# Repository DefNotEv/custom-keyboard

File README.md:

A description of what your project is
A couple sentences on why you made the project

# piggy keyboard!!!

## description
this is a super basic 60% keyboard with akko steller rose switches. it's completely custom: the pcb, cad, and plate files are all in here. 

## why i made it!
i've been talking about making a keyboard since the pandemic started but i am BROKE (that's a fancy way of saying i'm lazy) so when i found out i can do it all FOR FREE??? HELLO???? YES PLEASE??? 

## but uh...
bro initially i wanted to make this a tkl but tell me why kicad keybaord schematics are so difficult and for what??? like an rp2040 is NOT that complicated why am i struggling to trace capacitors. anyway. had to dumb it down. i hope i can make another tkl later. somebody please teach me how to proprely make pcbs.

## stfu ev show me the pictures
i gotchu

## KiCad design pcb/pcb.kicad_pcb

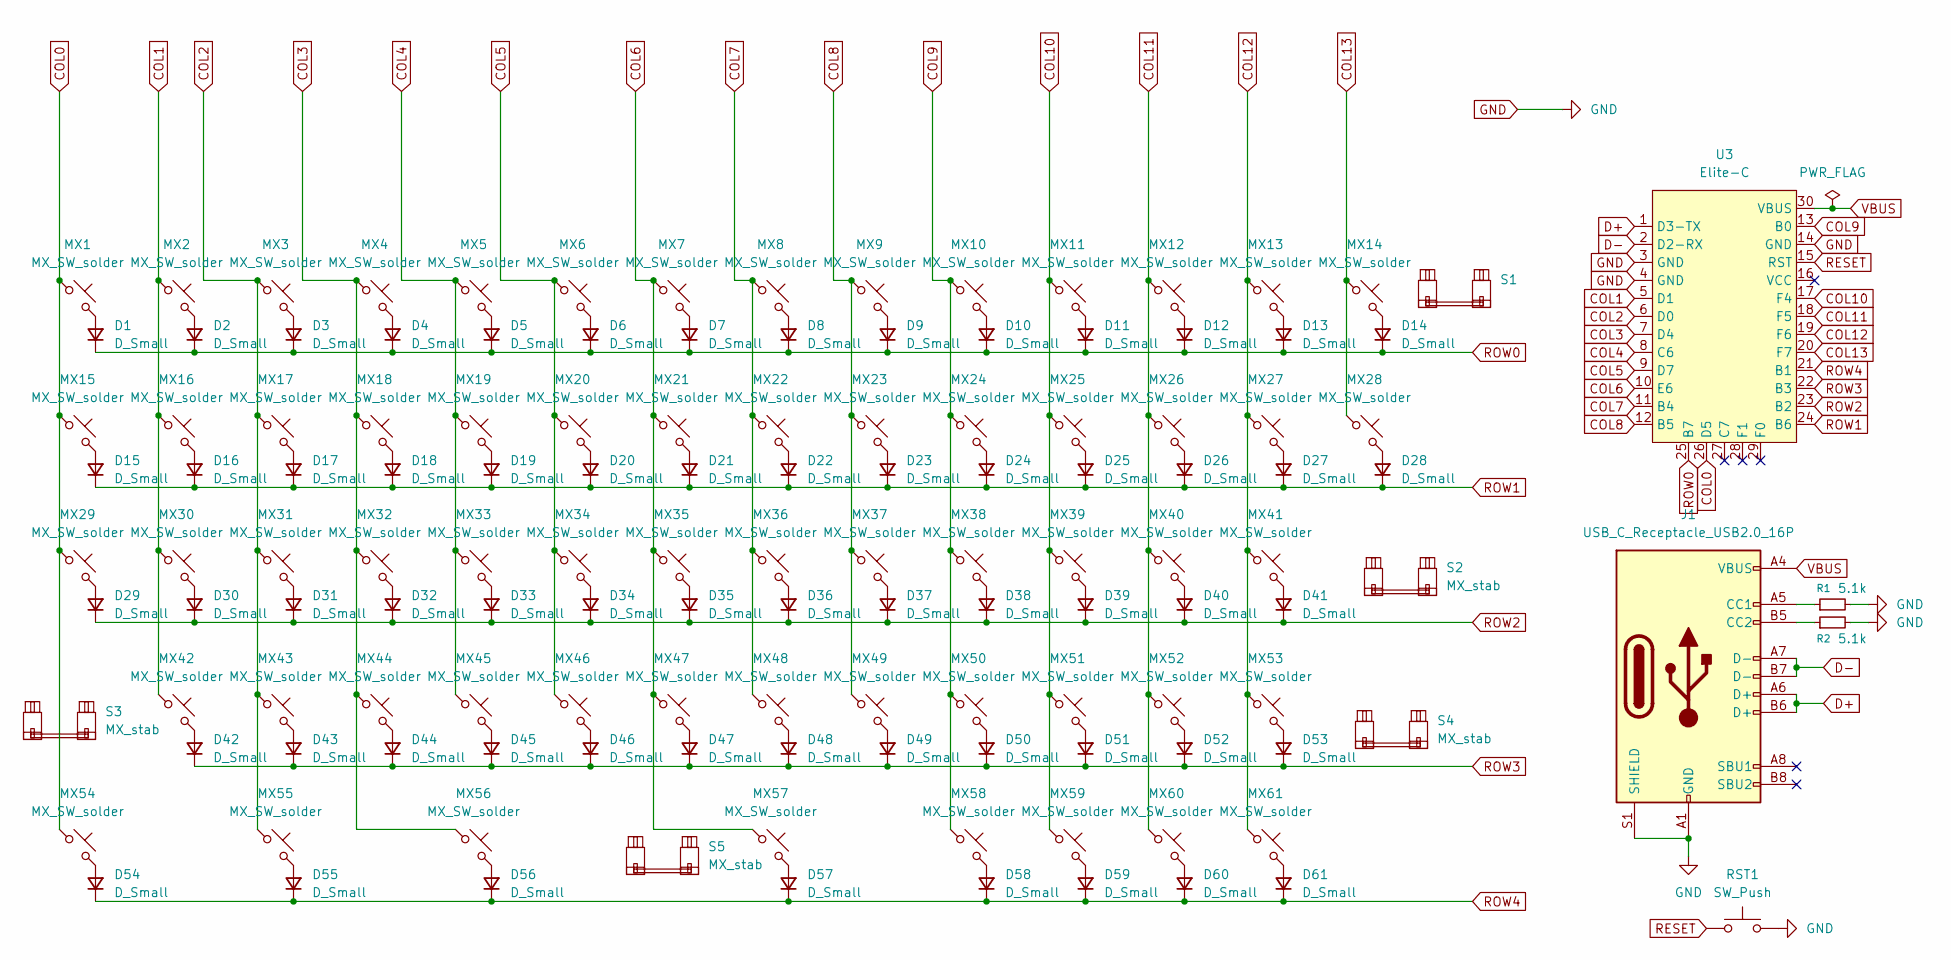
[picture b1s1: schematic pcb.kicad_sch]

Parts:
D1, D2, D3, D4, D5, D6, D7, D8, D9, D10, D11, D12, D13, D14, D15, D16, D17, D18, D19, D20, D21, D22, D23, D24, D25, D26, D27, D28, D29, D30, D31, D32, D33, D34, D35, D36, D37, D38, D39, D40, D41, D42, D43, D44, D45, D46, D47, D48, D49, D50, D51, D52, D53, D54, D55, D56, D57, D58, D59, D60, D61: D_Small; D_SOD-123
J1: USB_C_Receptacle_USB2.0_16P; USB_C_Receptacle_HRO_TYPE-C-31-M-12
MX1, MX2, MX3, MX4, MX5, MX6, MX7, MX8, MX9, MX10, MX11, MX12, MX13, MX14, MX16, MX17, MX18, MX19, MX20, MX21, MX22, MX23, MX24, MX25, MX26, MX27, MX30, MX31, MX32, MX33, MX34, MX35, MX36, MX37, MX38, MX39, MX40, MX41, MX42, MX43, MX44, MX45, MX46, MX47, MX48, MX49, MX50, MX51, MX52, MX53, MX57: MX_SW_solder; SW_MX_1u
MX15, MX28: MX_SW_solder; SW_MX_1.5u
MX29: MX_SW_solder; SW_MX_1.75u
MX54, MX55, MX56, MX58, MX59, MX60, MX61: MX_SW_solder; SW_MX_1.25u
R1, R2: 5.1k; R_0402_1005Metric
RST1: SW_Push; SW_SPST_TL3305B
S1, S2, S3, S4: MX_stab; STAB_MX_P_2u
S5: MX_stab; STAB_MX_P_6.25u
U3: Elite-C; Elite-C_ACH

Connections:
COL0: MX1.1, MX15.1, MX29.1, MX54.1, U3.26 (D5)
COL1: MX2.1, MX16.1, MX30.1, MX42.1, U3.5 (D1)
COL2: MX3.1, MX17.1, MX31.1, MX43.1, MX55.1, U3.6 (D0)
COL3: MX4.1, MX18.1, MX32.1, MX44.1, MX56.1, U3.7 (D4)
COL4: MX5.1, MX19.1, MX33.1, MX45.1, U3.8 (C6)
COL5: MX6.1, MX20.1, MX34.1, MX46.1, U3.9 (D7)
COL6: MX7.1, MX21.1, MX35.1, MX47.1, MX57.1, U3.10 (E6)
COL7: MX8.1, MX22.1, MX36.1, MX48.1, U3.11 (B4)
COL8: MX9.1, MX23.1, MX37.1, MX49.1, U3.12 (B5)
COL9: MX10.1, MX24.1, MX38.1, MX50.1, MX58.1, U3.13 (B0)
COL10: MX11.1, MX25.1, MX39.1, MX51.1, MX59.1, U3.17 (F4)
COL11: MX12.1, MX26.1, MX40.1, MX52.1, MX60.1, U3.18 (F5)
COL12: MX13.1, MX27.1, MX41.1, MX53.1, MX61.1, U3.19 (F6)
COL13: MX14.1, MX28.1, U3.20 (F7)
D+: J1.A6 (D+), J1.B6 (D+), U3.1 (D3-TX)
D-: J1.A7 (D-), J1.B7 (D-), U3.2 (D2-RX)
GND: J1.A1 (GND), J1.A12 (GND), J1.B1 (GND), J1.B12 (GND), J1.S1 (SHIELD), R1.2, R2.2, RST1.2, U3.3 (GND), U3.4 (GND), U3.14 (GND)
unnamed: D1.2 (A), MX1.2
unnamed: D2.2 (A), MX2.2
unnamed: D3.2 (A), MX3.2
unnamed: D4.2 (A), MX4.2
unnamed: D5.2 (A), MX5.2
unnamed: D6.2 (A), MX6.2
unnamed: D7.2 (A), MX7.2
unnamed: D8.2 (A), MX8.2
unnamed: D9.2 (A), MX9.2
unnamed: D10.2 (A), MX10.2
unnamed: D11.2 (A), MX11.2
unnamed: D12.2 (A), MX12.2
unnamed: D13.2 (A), MX13.2
unnamed: D14.2 (A), MX14.2
unnamed: D15.2 (A), MX15.2
unnamed: D16.2 (A), MX16.2
unnamed: D17.2 (A), MX17.2
unnamed: D18.2 (A), MX18.2
unnamed: D19.2 (A), MX19.2
unnamed: D20.2 (A), MX20.2
unnamed: D21.2 (A), MX21.2
unnamed: D22.2 (A), MX22.2
unnamed: D23.2 (A), MX23.2
unnamed: D24.2 (A), MX24.2
unnamed: D25.2 (A), MX25.2
unnamed: D26.2 (A), MX26.2
unnamed: D27.2 (A), MX27.2
unnamed: D28.2 (A), MX28.2
unnamed: D29.2 (A), MX29.2
unnamed: D30.2 (A), MX30.2
unnamed: D31.2 (A), MX31.2
unnamed: D32.2 (A), MX32.2
unnamed: D33.2 (A), MX33.2
unnamed: D34.2 (A), MX34.2
unnamed: D35.2 (A), MX35.2
unnamed: D36.2 (A), MX36.2
unnamed: D37.2 (A), MX37.2
unnamed: D38.2 (A), MX38.2
unnamed: D39.2 (A), MX39.2
unnamed: D40.2 (A), MX40.2
unnamed: D41.2 (A), MX41.2
unnamed: D42.2 (A), MX42.2
unnamed: D43.2 (A), MX43.2
unnamed: D44.2 (A), MX44.2
unnamed: D45.2 (A), MX45.2
unnamed: D46.2 (A), MX46.2
unnamed: D47.2 (A), MX47.2
unnamed: D48.2 (A), MX48.2
unnamed: D49.2 (A), MX49.2
unnamed: D50.2 (A), MX50.2
unnamed: D51.2 (A), MX51.2
unnamed: D52.2 (A), MX52.2
unnamed: D53.2 (A), MX53.2
unnamed: D54.2 (A), MX54.2
unnamed: D55.2 (A), MX55.2
unnamed: D56.2 (A), MX56.2
unnamed: D57.2 (A), MX57.2
unnamed: D58.2 (A), MX58.2
unnamed: D59.2 (A), MX59.2
unnamed: D60.2 (A), MX60.2
unnamed: D61.2 (A), MX61.2
unnamed: J1.A5 (CC1), R1.1
unnamed: J1.B5 (CC2), R2.1
RESET: RST1.1, U3.15 (RST)
ROW0: D1.1 (K), D2.1 (K), D3.1 (K), D4.1 (K), D5.1 (K), D6.1 (K), D7.1 (K), D8.1 (K), D9.1 (K), D10.1 (K), D11.1 (K), D12.1 (K), D13.1 (K), D14.1 (K), U3.25 (B7)
ROW1: D15.1 (K), D16.1 (K), D17.1 (K), D18.1 (K), D19.1 (K), D20.1 (K), D21.1 (K), D22.1 (K), D23.1 (K), D24.1 (K), D25.1 (K), D26.1 (K), D27.1 (K), D28.1 (K), U3.24 (B6)
ROW2: D29.1 (K), D30.1 (K), D31.1 (K), D32.1 (K), D33.1 (K), D34.1 (K), D35.1 (K), D36.1 (K), D37.1 (K), D38.1 (K), D39.1 (K), D40.1 (K), D41.1 (K), U3.23 (B2)
ROW3: D42.1 (K), D43.1 (K), D44.1 (K), D45.1 (K), D46.1 (K), D47.1 (K), D48.1 (K), D49.1 (K), D50.1 (K), D51.1 (K), D52.1 (K), D53.1 (K), U3.22 (B3)
ROW4: D54.1 (K), D55.1 (K), D56.1 (K), D57.1 (K), D58.1 (K), D59.1 (K), D60.1 (K), D61.1 (K), U3.21 (B1)
VBUS: J1.A4 (VBUS), J1.A9 (VBUS), J1.B4 (VBUS), J1.B9 (VBUS), U3.30 (VBUS)

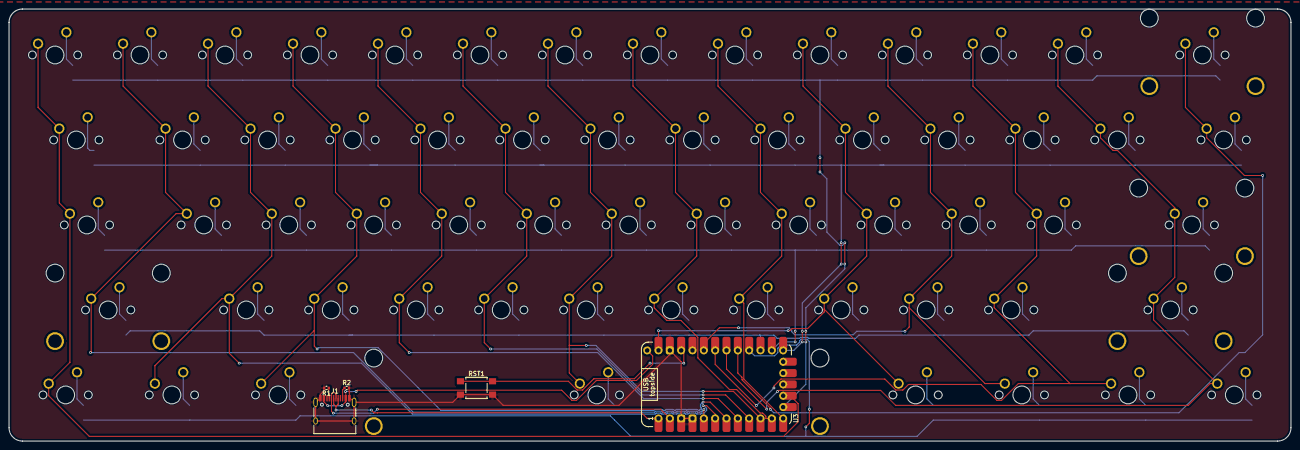
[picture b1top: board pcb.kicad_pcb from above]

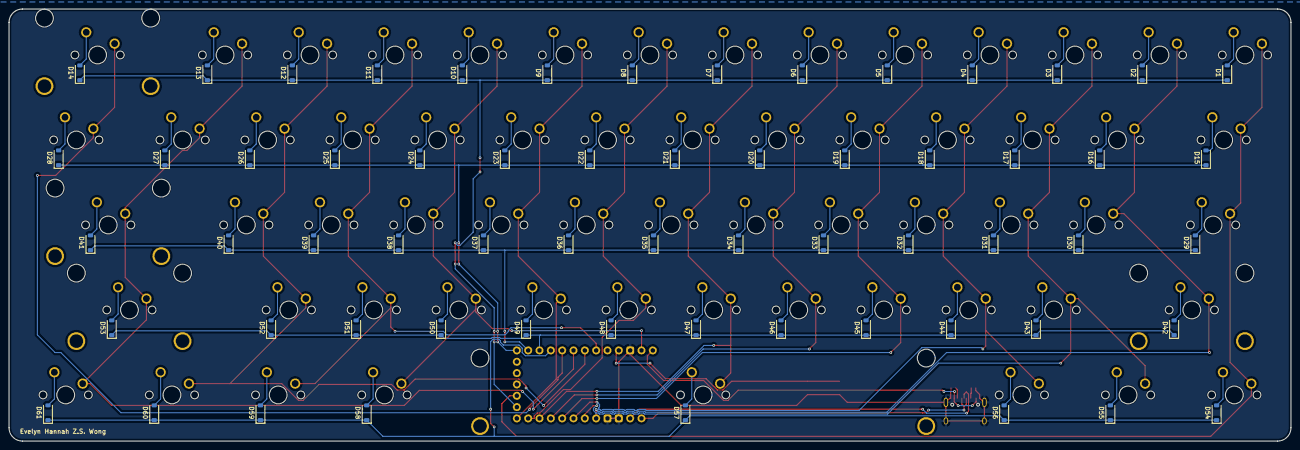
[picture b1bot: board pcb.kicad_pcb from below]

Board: 2 copper layers, 287.3 x 96.8 mm, 132 parts (61 on the bottom side), 87 nets.

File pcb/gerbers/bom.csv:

"Reference","Qty","Value","DNP","Exclude from BOM","Exclude from Board","Footprint","Datasheet"
"D1,D2,D3,D4,D5,D6,D7,D8,D9,D10,D11,D12,D13,D14,D15,D16,D17,D18,D19,D20,D21,D22,D23,D24,D25,D26,D27,D28,D29,D30,D31,D32,D33,D34,D35,D36,D37,D38,D39,D40,D41,D42,D43,D44,D45,D46,D47,D48,D49,D50,D51,D52,D53,D54,D55,D56,D57,D58,D59,D60,D61","61","D_Small","","","","Diode_SMD:D_SOD-123","~"
"J1","1","USB_C_Receptacle_USB2.0_16P","","","","Connector_USB:USB_C_Receptacle_HRO_TYPE-C-31-M-12","https://www.usb.org/sites/default/files/documents/usb_type-c.zip"
"MX1,MX2,MX3,MX4,MX5,MX6,MX7,MX8,MX9,MX10,MX11,MX12,MX13,MX14,MX16,MX17,MX18,MX19,MX20,MX21,MX22,MX23,MX24,MX25,MX26,MX27,MX30,MX31,MX32,MX33,MX34,MX35,MX36,MX37,MX38,MX39,MX40,MX41,MX42,MX43,MX44,MX45,MX46,MX47,MX48,MX49,MX50,MX51,MX52,MX53,MX57","51","MX_SW_solder","","","","PCM_marbastlib-mx:SW_MX_1u","~"
"MX15,MX28","2","MX_SW_solder","","","","PCM_marbastlib-mx:SW_MX_1.5u","~"
"MX29","1","MX_SW_solder","","","","PCM_marbastlib-mx:SW_MX_1.75u","~"
"MX54,MX55,MX56,MX58,MX59,MX60,MX61","7","MX_SW_solder","","","","PCM_marbastlib-mx:SW_MX_1.25u","~"
"R1,R2","2","5.1k","","","","Resistor_SMD:R_0402_1005Metric","~"
"RST1","1","SW_Push","","","","Button_Switch_SMD:SW_SPST_TL3305B","~"
"S1,S2,S3,S4","4","MX_stab","","","","PCM_marbastlib-mx:STAB_MX_P_2u",""
"S5","1","MX_stab","","","","PCM_marbastlib-mx:STAB_MX_P_6.25u",""
"U3","1","Elite-C","","Excluded from BOM","","PCM_marbastlib-xp-promicroish:Elite-C_ACH",""

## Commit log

2025-06-18 oops
2025-06-18 journal
2025-06-18 jourrnal
2025-06-18 images
2025-06-18 i forgot how to use kicad
2025-06-18 pcbs suck bruh
2025-06-19 timestamps
2025-06-22 ahhhhhhhhhhhhhh
2025-06-22 woooo
2025-06-22 fml!
2025-06-22 sleep
2025-06-22 i just learned how journals worked
2025-06-22 times
2025-06-22 fix headings
2025-06-22 readme
    lowkey just did that for the minutes on hackatime
